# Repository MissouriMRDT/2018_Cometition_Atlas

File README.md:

# 2018_Cometition_Atlas
All Hardware and Software Files used in the 2018 Competition

How to add repos to this while retaining commit history:

1. Clone this repo onto your pc
2. Make branch on here for the repo you're about to copy in
3. Make sure that you've merged the final release branch of the target repo into master
4. In gitshell inside of the 2018 Competition Atlas folder:

git checkout [name of branch you're going to copy the repo into]

git remote add x [url of deprecated repo]

git fetch x

git merge x/master --allow-unrelated-histories

git remote rm x

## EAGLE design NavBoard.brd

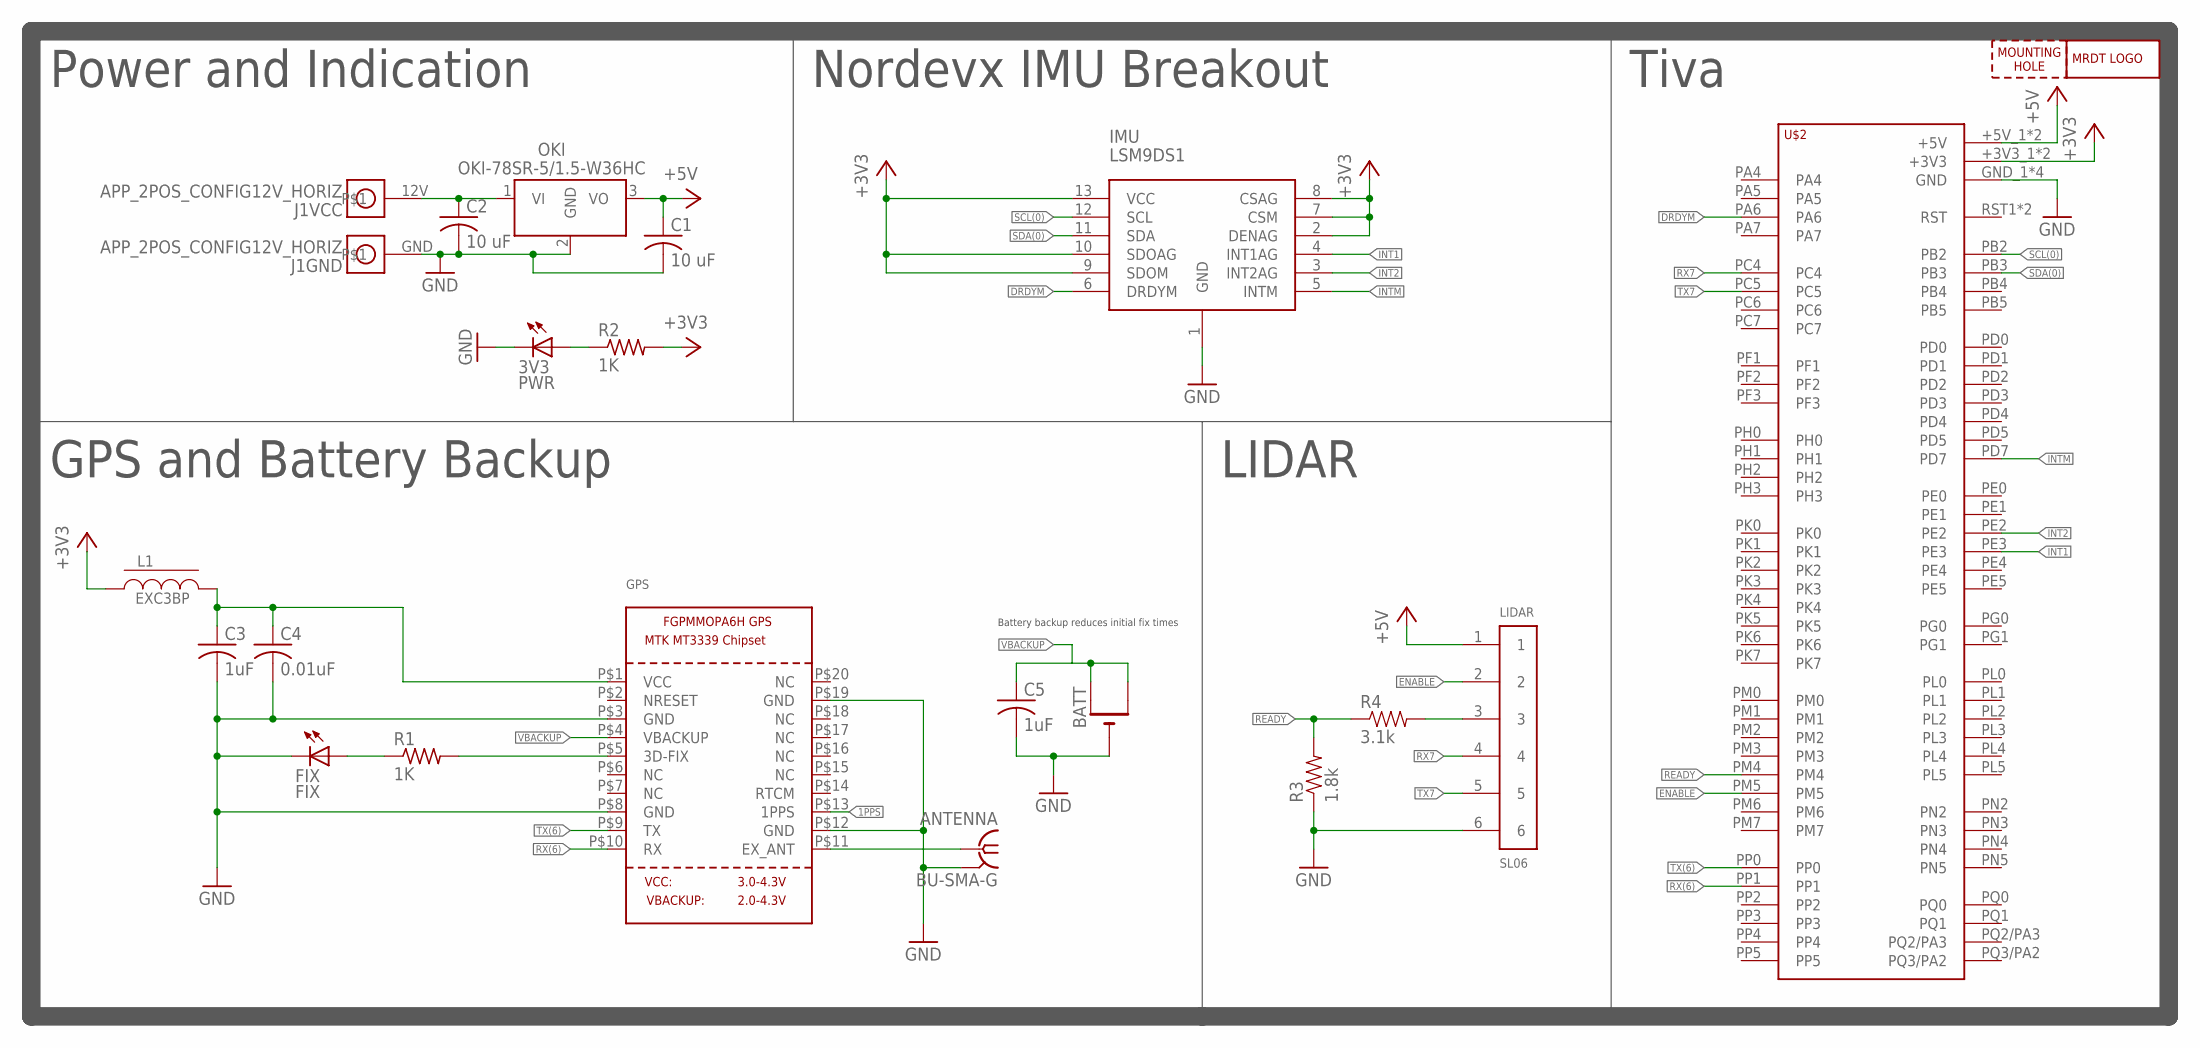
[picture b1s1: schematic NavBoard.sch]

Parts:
3V3: PWR; CHIPLED_0805
ANTENNA: BU-SMA-G
BATT: CR1220SMT; CR1220-SMD
C1, C2: 10 uF; C1206
C3, C5: 1uF; C0805
C4: 0.01uF; C0805
FIX: FIX; CHIPLED_0805
GPS: GPS_FGPMMOPA6H; FGPMMOPA6H
H1: MOUNTING_HOLE#6; #6_SCREW
IMU: LSM9DS1; LSM9DS1_BREAKOUT
J1: APP_2POS_CONFIG12V_HORIZ; APP45_12V_HORIZ_CONFIG
L1: EXC3BP; L0603
LIDAR: SL06; MOLEX_SL_06_TH
LOGO1: MRDT_LOGO
OKI: OKI-78SR-5/1.5-W36HC; OKI-78SR_HORIZ
R1, R2: 1K; M0805
R3: 1.8k; 0805
R4: 3.1k; 0805
U$2: TIVA-1294; TIVA-C-CONNECTED

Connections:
1PPS: GPS.P$13 (1PPS)
3V3: C3.1, C4.1, GPS.P$1 (VCC), L1.2
12V: C2.1, J1.12V, OKI.1 (VI)
+3V3: IMU.2 (DENAG), IMU.7 (CSM), IMU.8 (CSAG), IMU.9 (SDOM), IMU.10 (SDOAG), IMU.13 (VCC), L1.1, R2.2, U$2.+3V3_1 (+3V3), U$2.+3V3_2 (+3V3)
+5V: C1.1, LIDAR.1, OKI.3 (VO), U$2.+5V_1 (+5V), U$2.+5V_2 (+5V)
DRDYM: IMU.6 (DRDYM), U$2.PA6
ENABLE: LIDAR.2, U$2.PM5
GND: 3V3.C, ANTENNA.2, ANTENNA.3 (2), ANTENNA.4 (2), ANTENNA.5 (2), BATT.-, C1.2, C2.2, C3.2, C4.2, C5.2, FIX.C, GPS.P$3 (GND), GPS.P$8 (GND), GPS.P$12 (GND), GPS.P$19 (GND), IMU.1 (GND), J1.GND, LIDAR.6, OKI.2 (GND), R3.1, U$2.GND_1 (GND), U$2.GND_2 (GND), U$2.GND_3 (GND), U$2.GND_4 (GND)
INT1: IMU.4 (INT1AG), U$2.PE3
INT2: IMU.3 (INT2AG), U$2.PE2
INTM: IMU.5 (INTM), U$2.PD7
unnamed: FIX.A, R1.1
unnamed: GPS.P$5 (3D-FIX), R1.2
unnamed: 3V3.A, R2.1
unnamed: ANTENNA.1, GPS.P$11 (EX_ANT)
unnamed: LIDAR.3, R4.2
READY: R3.2, R4.1, U$2.PM4
RX7: LIDAR.4, U$2.PC4
RX(6): GPS.P$10 (RX), U$2.PP1
SCL(0): IMU.12 (SCL), U$2.PB2
SDA(0): IMU.11 (SDA), U$2.PB3
TX7: LIDAR.5, U$2.PC5
TX(6): GPS.P$9 (TX), U$2.PP0
VBACKUP: BATT.+$1 (+), BATT.+$2 (+1), C5.1, GPS.P$4 (VBACKUP)

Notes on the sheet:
Power and Indication
Nordevx IMU Breakout
Tiva
GPS and Battery Backup
LIDAR
Battery backup reduces initial fix times

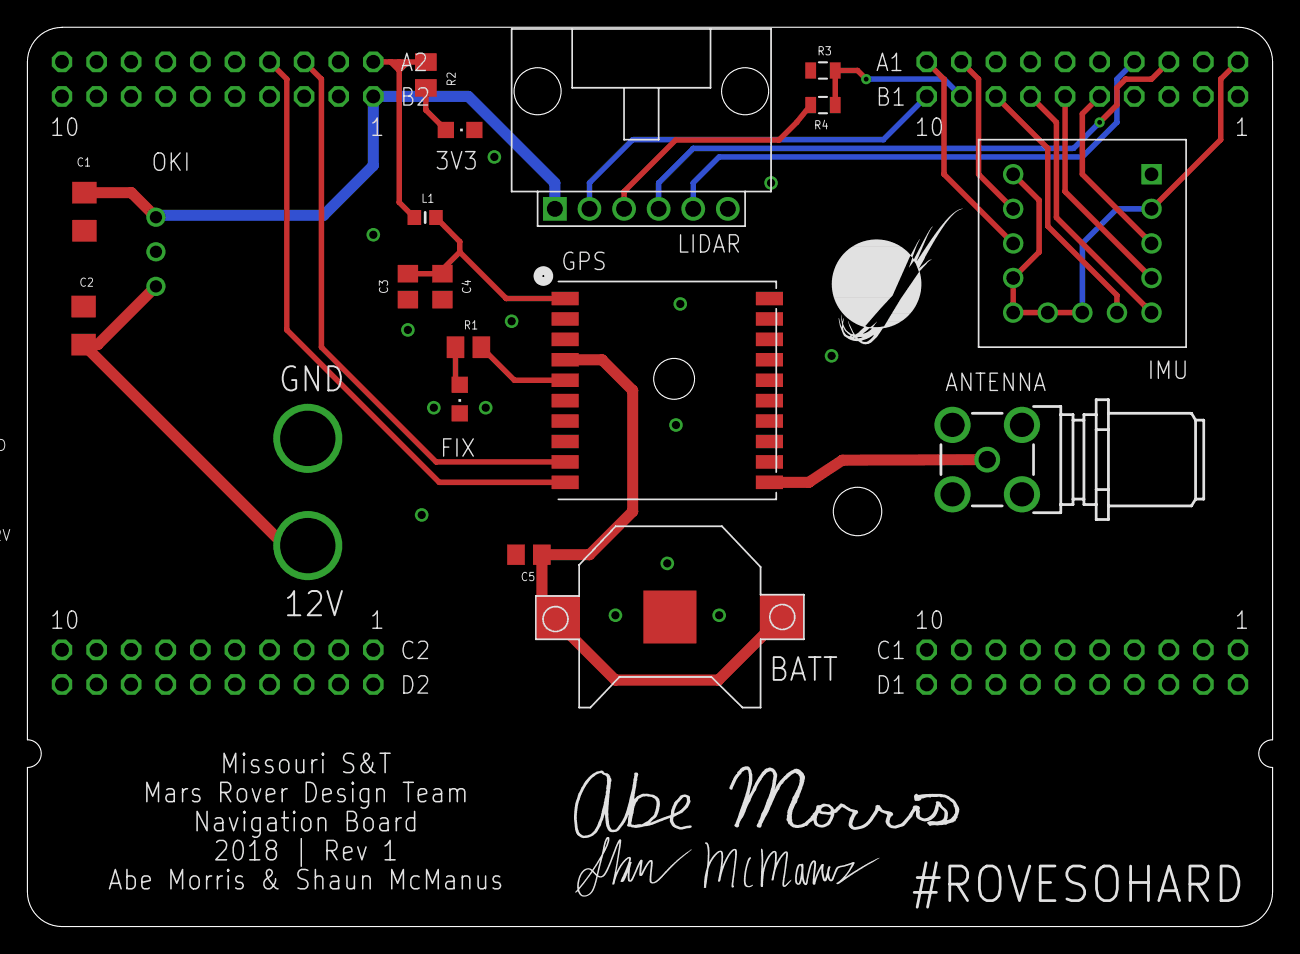
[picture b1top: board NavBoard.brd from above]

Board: 2 copper layers, 91.4 x 66.0 mm, 24 parts (0 on the bottom side), 23 nets.

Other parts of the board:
U$1: ABE_MORRIS_SIGNATURE
U$3: SHAUN_MCMANUS_SIGNATURE

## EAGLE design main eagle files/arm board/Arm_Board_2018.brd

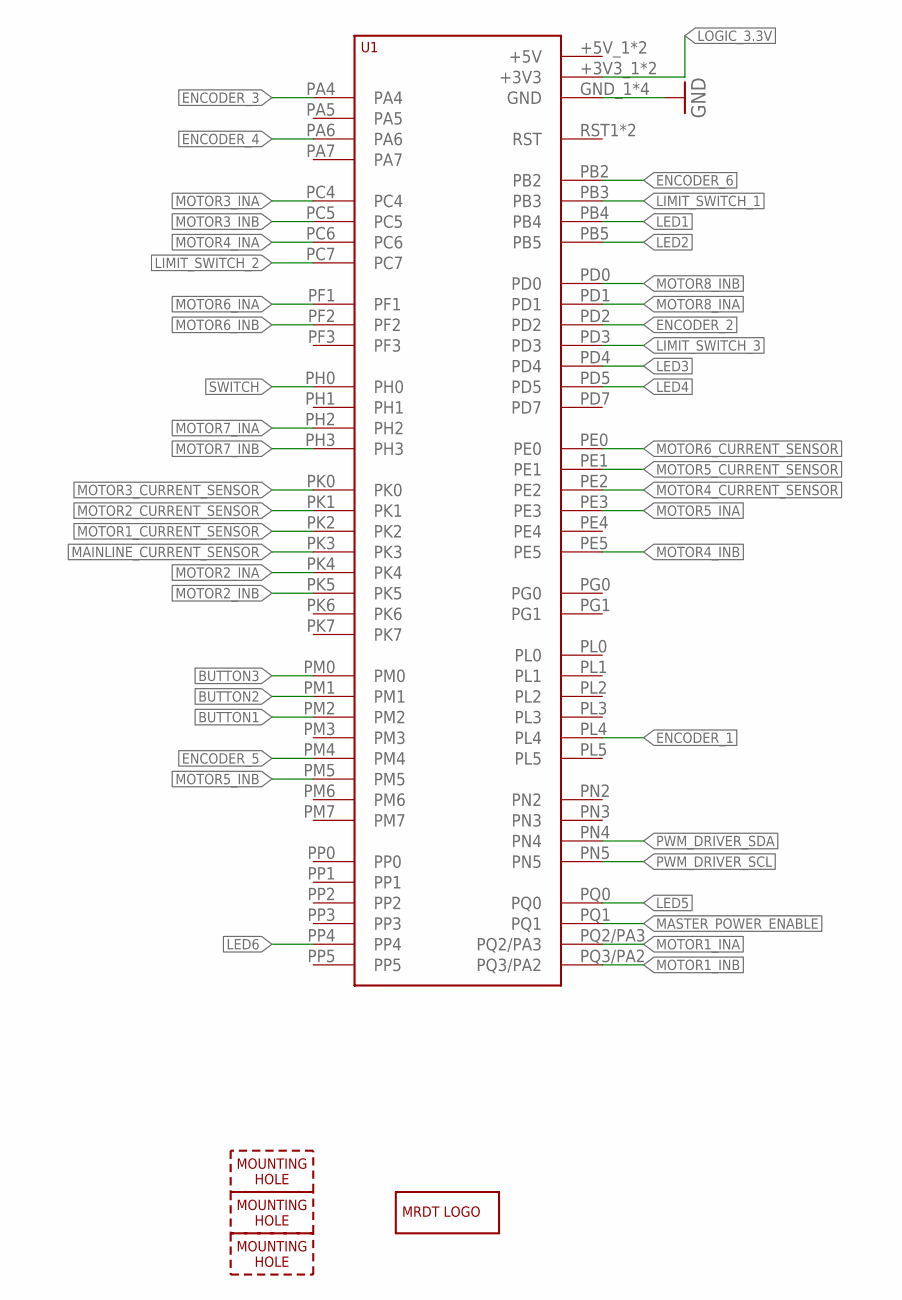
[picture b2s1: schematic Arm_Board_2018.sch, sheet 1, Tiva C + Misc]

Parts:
H1, H2, H3: MOUNTING_HOLE#6; #6_SCREW
LOGO1: MRDT_LOGO
U1: TIVA-1294; TIVA-C-CONNECTED

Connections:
BUTTON1: U1.PM2; also elsewhere on the board
BUTTON2: U1.PM1; also elsewhere on the board
BUTTON3: U1.PM0; also elsewhere on the board
ENCODER_1: U1.PL4; also elsewhere on the board
ENCODER_2: U1.PD2; also elsewhere on the board
ENCODER_3: U1.PA4; also elsewhere on the board
ENCODER_4: U1.PA6; also elsewhere on the board
ENCODER_5: U1.PM4; also elsewhere on the board
ENCODER_6: U1.PB2; also elsewhere on the board
GND: U1.GND_1 (GND), U1.GND_2 (GND), U1.GND_3 (GND), U1.GND_4 (GND); also elsewhere on the board
LED1: U1.PB4; also elsewhere on the board
LED2: U1.PB5; also elsewhere on the board
LED3: U1.PD4; also elsewhere on the board
LED4: U1.PD5; also elsewhere on the board
LED5: U1.PQ0; also elsewhere on the board
LED6: U1.PP4; also elsewhere on the board
LIMIT_SWITCH_1: U1.PB3; also elsewhere on the board
LIMIT_SWITCH_2: U1.PC7; also elsewhere on the board
LIMIT_SWITCH_3: U1.PD3; also elsewhere on the board
LOGIC_3.3V: U1.+3V3_1 (+3V3), U1.+3V3_2 (+3V3); also elsewhere on the board
MAINLINE_CURRENT_SENSOR: U1.PK3; also elsewhere on the board
MASTER_POWER_ENABLE: U1.PQ1; also elsewhere on the board
MOTOR1_CURRENT_SENSOR: U1.PK2; also elsewhere on the board
MOTOR1_INA: U1.PQ2/PA3; also elsewhere on the board
MOTOR1_INB: U1.PQ3/PA2; also elsewhere on the board
MOTOR2_CURRENT_SENSOR: U1.PK1; also elsewhere on the board
MOTOR2_INA: U1.PK4; also elsewhere on the board
MOTOR2_INB: U1.PK5; also elsewhere on the board
MOTOR3_CURRENT_SENSOR: U1.PK0; also elsewhere on the board
MOTOR3_INA: U1.PC4; also elsewhere on the board
MOTOR3_INB: U1.PC5; also elsewhere on the board
MOTOR4_CURRENT_SENSOR: U1.PE2; also elsewhere on the board
MOTOR4_INA: U1.PC6; also elsewhere on the board
MOTOR4_INB: U1.PE5; also elsewhere on the board
MOTOR5_CURRENT_SENSOR: U1.PE1; also elsewhere on the board
MOTOR5_INA: U1.PE3; also elsewhere on the board
MOTOR5_INB: U1.PM5; also elsewhere on the board
MOTOR6_CURRENT_SENSOR: U1.PE0; also elsewhere on the board
MOTOR6_INA: U1.PF1; also elsewhere on the board
MOTOR6_INB: U1.PF2; also elsewhere on the board
MOTOR7_INA: U1.PH2; also elsewhere on the board
MOTOR7_INB: U1.PH3; also elsewhere on the board
MOTOR8_INA: U1.PD1; also elsewhere on the board
MOTOR8_INB: U1.PD0; also elsewhere on the board
PWM_DRIVER_SCL: U1.PN5; also elsewhere on the board
PWM_DRIVER_SDA: U1.PN4; also elsewhere on the board
SWITCH: U1.PH0; also elsewhere on the board

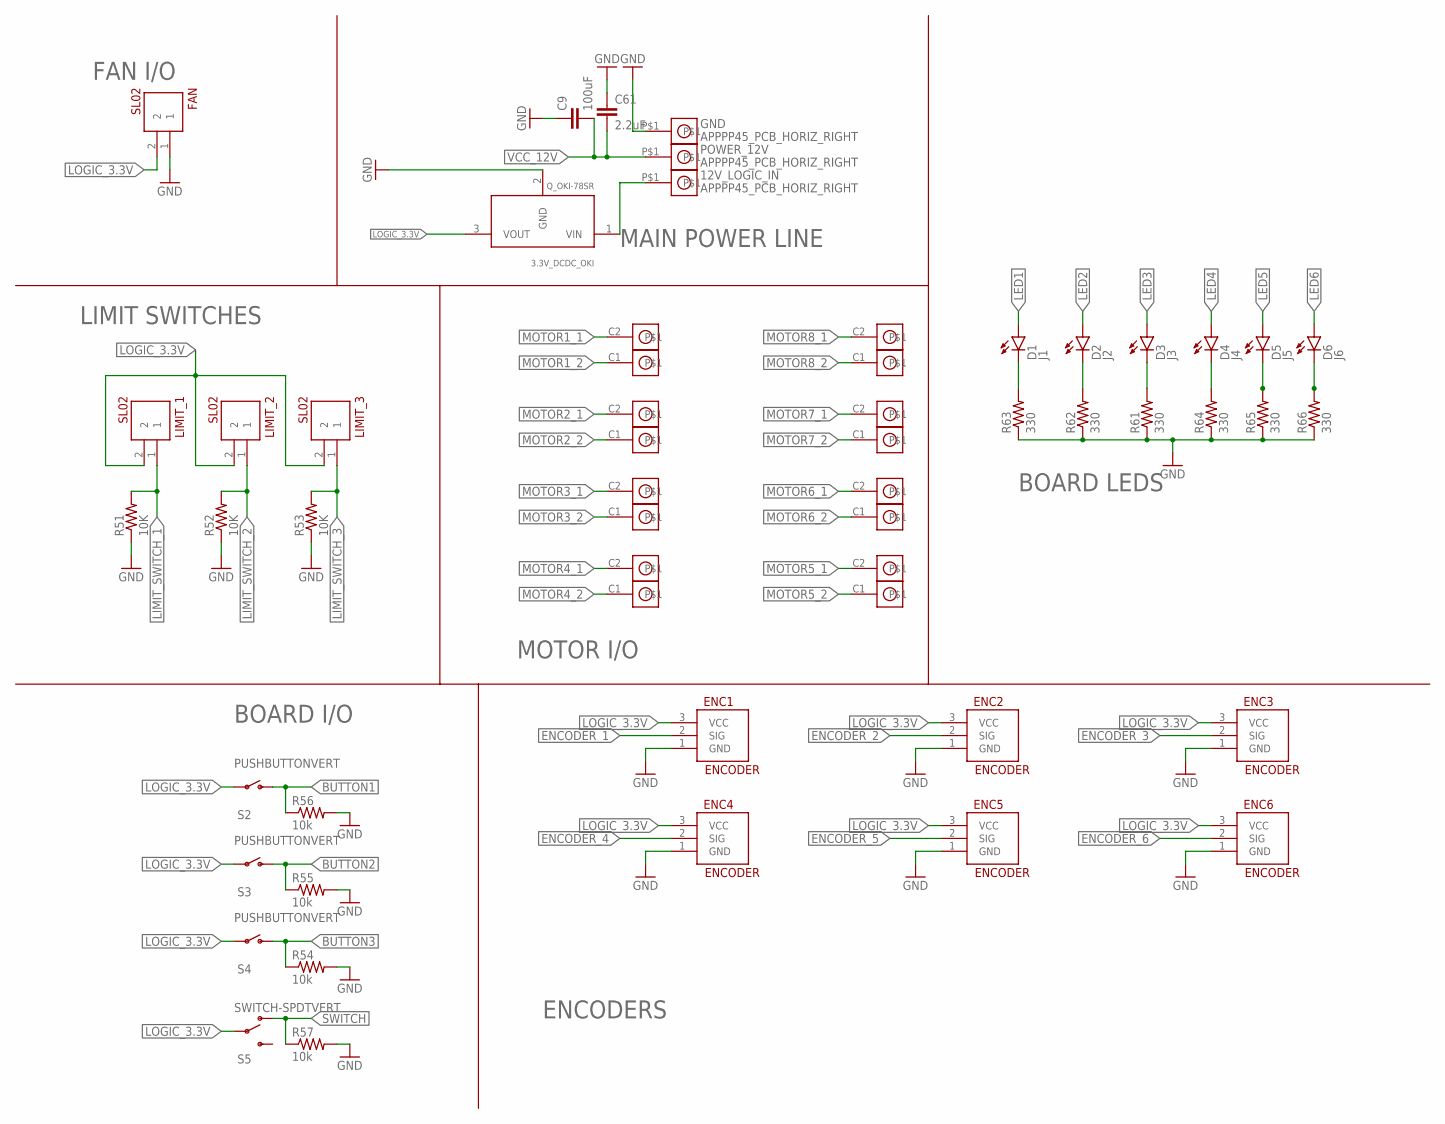
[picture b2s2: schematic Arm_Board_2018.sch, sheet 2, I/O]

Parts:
3.3V_DCDC_OKI: Q_OKI-78SR
12V_LOGIC_IN: APPPP45_PCB_HORIZ_RIGHT; APP45_PCB_HORIZ_RIGHT
C9: 100uF; 1210
C61: 2.2uF; 1206
D1: J1; LED-0603
D2: J2; LED-0603
D3: J3; LED-0603
D4: J4; LED-0603
D5: J5; LED-0603
D6: J6; LED-0603
ENC1, ENC2, ENC3, ENC4, ENC5, ENC6: ENCODER; MOLEX-70543-0002
FAN: SL02; MOLEX-70543-0001
GND: APPPP45_PCB_HORIZ_RIGHT; APP45_PCB_HORIZ_RIGHT
LIMIT_1, LIMIT_2, LIMIT_3: SL02; MOLEX-70543-0001
MOTOR1, MOTOR2, MOTOR3, MOTOR4, MOTOR5, MOTOR6, MOTOR7, MOTOR8: APP_2POS_CONFIGGENERAL_CONFIG; APP45_HORIZ_CONFIG
POWER_12V: APPPP45_PCB_HORIZ_RIGHT; APP45_PCB_HORIZ_RIGHT
R51, R52, R53: 10K; 0402-RES
R54, R55, R56, R57: 10k; 0402-RES
R61, R62, R63, R64, R65, R66: 330; 0402-RES
S2, S3, S4: PUSHBUTTONVERT; APEM-MJTP1243
S5: SWITCH-SPDTVERT; C&K-SS12D07VG4NSGAPA

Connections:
BUTTON1: R56.1, S2.P$2 (S); also elsewhere on the board
BUTTON2: R55.1, S3.P$2 (S); also elsewhere on the board
BUTTON3: R54.1, S4.P$2 (S); also elsewhere on the board
ENCODER_1: ENC1.2 (SIG); also elsewhere on the board
ENCODER_2: ENC2.2 (SIG); also elsewhere on the board
ENCODER_3: ENC3.2 (SIG); also elsewhere on the board
ENCODER_4: ENC4.2 (SIG); also elsewhere on the board
ENCODER_5: ENC5.2 (SIG); also elsewhere on the board
ENCODER_6: ENC6.2 (SIG); also elsewhere on the board
GND: 3.3V_DCDC_OKI.2 (GND), C9.1, C61.1, ENC1.1 (GND), ENC2.1 (GND), ENC3.1 (GND), ENC4.1 (GND), ENC5.1 (GND), ENC6.1 (GND), FAN.1, GND.P$1, R51.1, R52.1, R53.1, R54.2, R55.2, R56.2, R57.2, R61.1, R62.1, R63.1, R64.1, R65.1, R66.1; also elsewhere on the board
LED1: D1.A; also elsewhere on the board
LED2: D2.A; also elsewhere on the board
LED3: D3.A; also elsewhere on the board
LED4: D4.A; also elsewhere on the board
LED5: D5.A; also elsewhere on the board
LED6: D6.A; also elsewhere on the board
LIMIT_SWITCH_1: LIMIT_1.1, R51.2; also elsewhere on the board
LIMIT_SWITCH_2: LIMIT_2.1, R52.2; also elsewhere on the board
LIMIT_SWITCH_3: LIMIT_3.1, R53.2; also elsewhere on the board
LOGIC_3.3V: 3.3V_DCDC_OKI.3 (VOUT), ENC1.3 (VCC), ENC2.3 (VCC), ENC3.3 (VCC), ENC4.3 (VCC), ENC5.3 (VCC), ENC6.3 (VCC), FAN.2, LIMIT_1.2, LIMIT_2.2, LIMIT_3.2, S2.P$1, S3.P$1, S4.P$1, S5.P$2; also elsewhere on the board
MOTOR1_1: MOTOR1.C2; also elsewhere on the board
MOTOR1_2: MOTOR1.C1; also elsewhere on the board
MOTOR2_1: MOTOR2.C2; also elsewhere on the board
MOTOR2_2: MOTOR2.C1; also elsewhere on the board
MOTOR3_1: MOTOR3.C2; also elsewhere on the board
MOTOR3_2: MOTOR3.C1; also elsewhere on the board
MOTOR4_1: MOTOR4.C2; also elsewhere on the board
MOTOR4_2: MOTOR4.C1; also elsewhere on the board
MOTOR5_1: MOTOR5.C2; also elsewhere on the board
MOTOR5_2: MOTOR5.C1; also elsewhere on the board
MOTOR6_1: MOTOR6.C2; also elsewhere on the board
MOTOR6_2: MOTOR6.C1; also elsewhere on the board
MOTOR7_1: MOTOR7.C2; also elsewhere on the board
MOTOR7_2: MOTOR7.C1; also elsewhere on the board
MOTOR8_1: MOTOR8.C2; also elsewhere on the board
MOTOR8_2: MOTOR8.C1; also elsewhere on the board
unnamed: 3.3V_DCDC_OKI.1 (VIN), 12V_LOGIC_IN.P$1
unnamed: D1.C, R63.2
unnamed: D2.C, R62.2
unnamed: D6.C, R66.2
unnamed: D3.C, R61.2
unnamed: D4.C, R64.2
unnamed: D5.C, R65.2
SWITCH: R57.1, S5.P$3 (O); also elsewhere on the board
VCC_12V: C9.2, C61.2, POWER_12V.P$1; also elsewhere on the board

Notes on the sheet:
FAN I/O
MOTOR I/O
MAIN POWER LINE
LIMIT SWITCHES
ENCODERS
BOARD I/O
BOARD LEDS

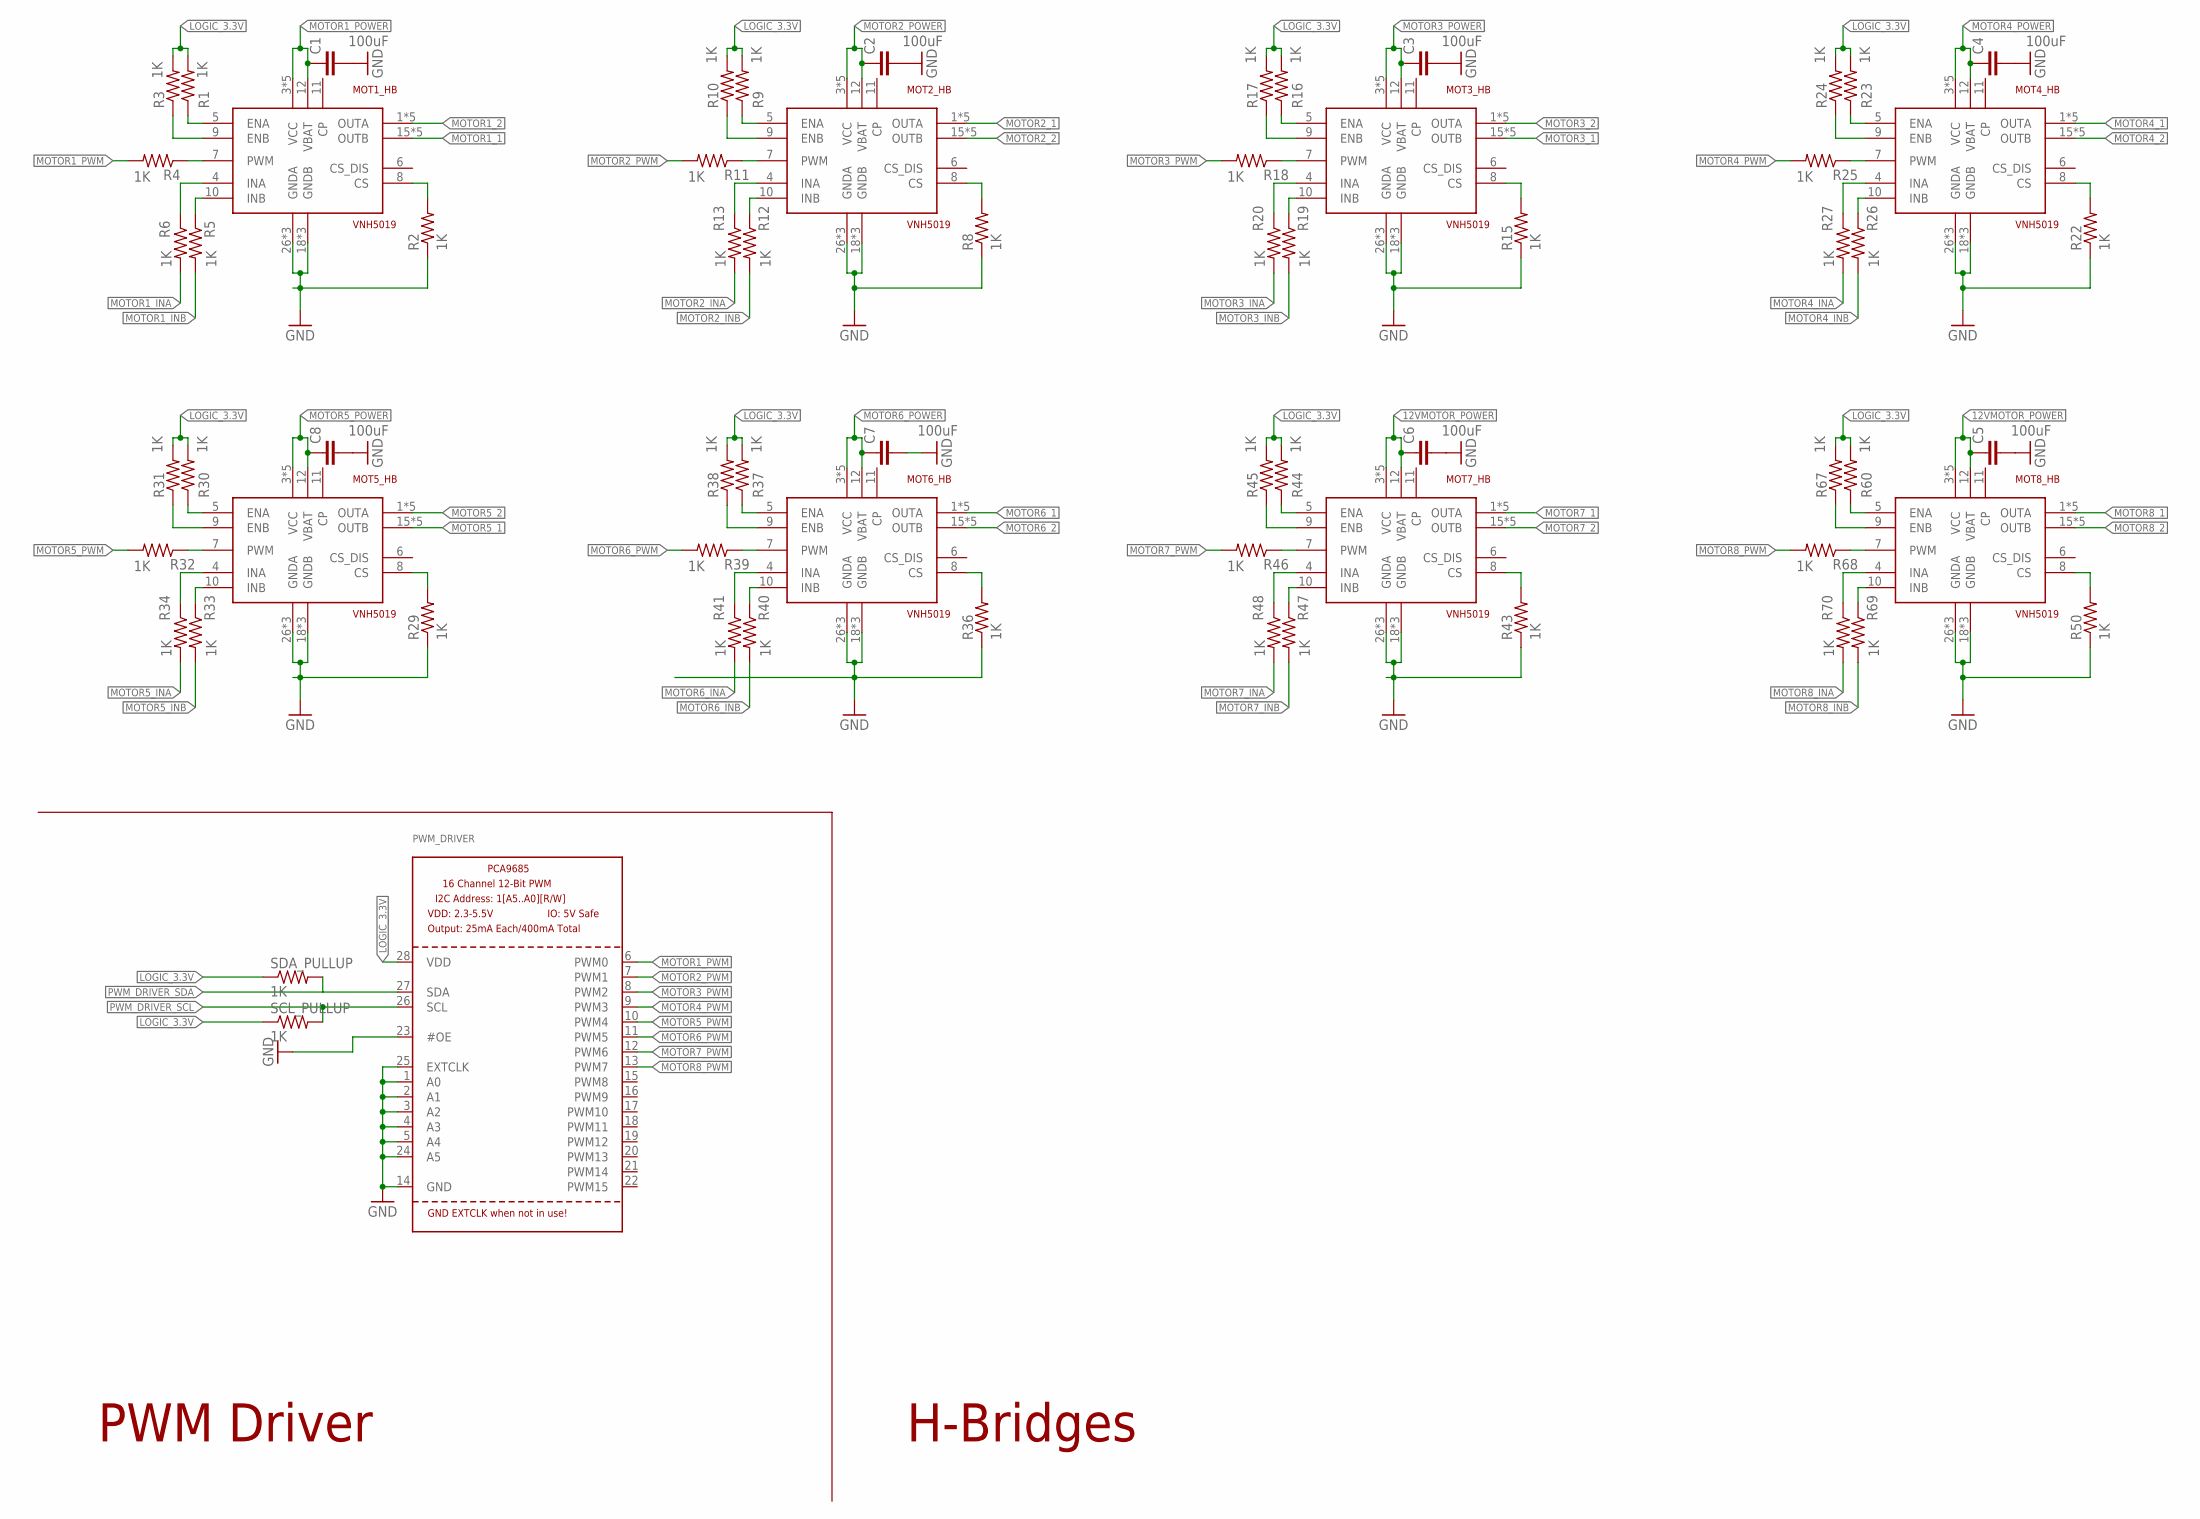
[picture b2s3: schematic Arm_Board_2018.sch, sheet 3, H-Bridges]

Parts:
C1, C2, C3, C4, C5, C6, C7, C8: 100uF; 1210
MOT1_HB, MOT2_HB, MOT3_HB, MOT4_HB, MOT5_HB, MOT6_HB, MOT7_HB, MOT8_HB: VNH5019; MULTIPOWERSO-30
PWM_DRIVER: PCA9685; TSSOP28
R1, R2, R3, R4, R5, R6, R8, R9, R10, R11, R12, R13, R15, R16, R17, R18, R19, R20, R22, R23, R24, R25, R26, R27, R29, R30, R31, R32, R33, R34, R36, R37, R38, R39, R40, R41, R43, R44, R45, R46, R47, R48, R50, R60, R67, R68, R69, R70: 1K; 0603-RES
SCL_PULLUP: 1K; 0402-RES
SDA_PULLUP: 1K; 0402-RES

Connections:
12VMOTOR_POWER: C5.1, C6.1, MOT7_HB.3 (VCC), MOT7_HB.12 (VBAT), MOT7_HB.13 (VCC), MOT7_HB.23 (VCC), MOT7_HB.VCC, MOT7_HB.VCC@1 (VCC), MOT8_HB.3 (VCC), MOT8_HB.12 (VBAT), MOT8_HB.13 (VCC), MOT8_HB.23 (VCC), MOT8_HB.VCC, MOT8_HB.VCC@1 (VCC); also elsewhere on the board
GND: C1.2, C2.2, C3.2, C4.2, C5.2, C6.2, C7.2, C8.2, MOT1_HB.18 (GNDB), MOT1_HB.19 (GNDB), MOT1_HB.20 (GNDB), MOT1_HB.26 (GNDA), MOT1_HB.27 (GNDA), MOT1_HB.28 (GNDA), MOT2_HB.18 (GNDB), MOT2_HB.19 (GNDB), MOT2_HB.20 (GNDB), MOT2_HB.26 (GNDA), MOT2_HB.27 (GNDA), MOT2_HB.28 (GNDA), MOT3_HB.18 (GNDB), MOT3_HB.19 (GNDB), MOT3_HB.20 (GNDB), MOT3_HB.26 (GNDA), MOT3_HB.27 (GNDA), MOT3_HB.28 (GNDA), MOT4_HB.18 (GNDB), MOT4_HB.19 (GNDB), MOT4_HB.20 (GNDB), MOT4_HB.26 (GNDA), MOT4_HB.27 (GNDA), MOT4_HB.28 (GNDA), MOT5_HB.18 (GNDB), MOT5_HB.19 (GNDB), MOT5_HB.20 (GNDB), MOT5_HB.26 (GNDA), MOT5_HB.27 (GNDA), MOT5_HB.28 (GNDA), MOT6_HB.18 (GNDB), MOT6_HB.19 (GNDB), MOT6_HB.20 (GNDB), MOT6_HB.26 (GNDA), MOT6_HB.27 (GNDA), MOT6_HB.28 (GNDA), MOT7_HB.18 (GNDB), MOT7_HB.19 (GNDB), MOT7_HB.20 (GNDB), MOT7_HB.26 (GNDA), MOT7_HB.27 (GNDA), MOT7_HB.28 (GNDA), MOT8_HB.18 (GNDB), MOT8_HB.19 (GNDB), MOT8_HB.20 (GNDB), MOT8_HB.26 (GNDA), MOT8_HB.27 (GNDA), MOT8_HB.28 (GNDA), PWM_DRIVER.1 (A0), PWM_DRIVER.2 (A1), PWM_DRIVER.3 (A2), PWM_DRIVER.4 (A3), PWM_DRIVER.5 (A4), PWM_DRIVER.14 (GND), PWM_DRIVER.23 (#OE), PWM_DRIVER.24 (A5), PWM_DRIVER.25 (EXTCLK), R2.1, R8.1, R15.1, R22.1, R29.1, R36.1, R43.1, R50.1; also elsewhere on the board
LOGIC_3.3V: PWM_DRIVER.28 (VDD), R1.2, R3.2, R9.2, R10.2, R16.2, R17.2, R23.2, R24.2, R30.2, R31.2, R37.2, R38.2, R44.2, R45.2, R60.2, R67.2, SCL_PULLUP.1, SDA_PULLUP.1; also elsewhere on the board
MOTOR1_1: MOT1_HB.15 (OUTB), MOT1_HB.16 (OUTB), MOT1_HB.21 (OUTB), MOT1_HB.OUTB, MOT1_HB.OUTB@1 (OUTB); also elsewhere on the board
MOTOR1_2: MOT1_HB.1 (OUTA), MOT1_HB.25 (OUTA), MOT1_HB.30 (OUTA), MOT1_HB.OUTA, MOT1_HB.OUTA@1 (OUTA); also elsewhere on the board
MOTOR1_INA: R6.2; also elsewhere on the board
MOTOR1_INB: R5.2; also elsewhere on the board
MOTOR1_POWER: C1.1, MOT1_HB.3 (VCC), MOT1_HB.12 (VBAT), MOT1_HB.13 (VCC), MOT1_HB.23 (VCC), MOT1_HB.VCC, MOT1_HB.VCC@1 (VCC); also elsewhere on the board
MOTOR1_PWM: PWM_DRIVER.6 (PWM0), R4.2
MOTOR2_1: MOT2_HB.1 (OUTA), MOT2_HB.25 (OUTA), MOT2_HB.30 (OUTA), MOT2_HB.OUTA, MOT2_HB.OUTA@1 (OUTA); also elsewhere on the board
MOTOR2_2: MOT2_HB.15 (OUTB), MOT2_HB.16 (OUTB), MOT2_HB.21 (OUTB), MOT2_HB.OUTB, MOT2_HB.OUTB@1 (OUTB); also elsewhere on the board
MOTOR2_INA: R13.2; also elsewhere on the board
MOTOR2_INB: R12.2; also elsewhere on the board
MOTOR2_POWER: C2.1, MOT2_HB.3 (VCC), MOT2_HB.12 (VBAT), MOT2_HB.13 (VCC), MOT2_HB.23 (VCC), MOT2_HB.VCC, MOT2_HB.VCC@1 (VCC); also elsewhere on the board
MOTOR2_PWM: PWM_DRIVER.7 (PWM1), R11.2
MOTOR3_1: MOT3_HB.15 (OUTB), MOT3_HB.16 (OUTB), MOT3_HB.21 (OUTB), MOT3_HB.OUTB, MOT3_HB.OUTB@1 (OUTB); also elsewhere on the board
MOTOR3_2: MOT3_HB.1 (OUTA), MOT3_HB.25 (OUTA), MOT3_HB.30 (OUTA), MOT3_HB.OUTA, MOT3_HB.OUTA@1 (OUTA); also elsewhere on the board
MOTOR3_INA: R20.2; also elsewhere on the board
MOTOR3_INB: R19.2; also elsewhere on the board
MOTOR3_POWER: C3.1, MOT3_HB.3 (VCC), MOT3_HB.12 (VBAT), MOT3_HB.13 (VCC), MOT3_HB.23 (VCC), MOT3_HB.VCC, MOT3_HB.VCC@1 (VCC); also elsewhere on the board
MOTOR3_PWM: PWM_DRIVER.8 (PWM2), R18.2
MOTOR4_1: MOT4_HB.1 (OUTA), MOT4_HB.25 (OUTA), MOT4_HB.30 (OUTA), MOT4_HB.OUTA, MOT4_HB.OUTA@1 (OUTA); also elsewhere on the board
MOTOR4_2: MOT4_HB.15 (OUTB), MOT4_HB.16 (OUTB), MOT4_HB.21 (OUTB), MOT4_HB.OUTB, MOT4_HB.OUTB@1 (OUTB); also elsewhere on the board
MOTOR4_INA: R27.2; also elsewhere on the board
MOTOR4_INB: R26.2; also elsewhere on the board
MOTOR4_POWER: C4.1, MOT4_HB.3 (VCC), MOT4_HB.12 (VBAT), MOT4_HB.13 (VCC), MOT4_HB.23 (VCC), MOT4_HB.VCC, MOT4_HB.VCC@1 (VCC); also elsewhere on the board
MOTOR4_PWM: PWM_DRIVER.9 (PWM3), R25.2
MOTOR5_1: MOT5_HB.15 (OUTB), MOT5_HB.16 (OUTB), MOT5_HB.21 (OUTB), MOT5_HB.OUTB, MOT5_HB.OUTB@1 (OUTB); also elsewhere on the board
MOTOR5_2: MOT5_HB.1 (OUTA), MOT5_HB.25 (OUTA), MOT5_HB.30 (OUTA), MOT5_HB.OUTA, MOT5_HB.OUTA@1 (OUTA); also elsewhere on the board
MOTOR5_INA: R34.2; also elsewhere on the board
MOTOR5_INB: R33.2; also elsewhere on the board
MOTOR5_POWER: C8.1, MOT5_HB.3 (VCC), MOT5_HB.12 (VBAT), MOT5_HB.13 (VCC), MOT5_HB.23 (VCC), MOT5_HB.VCC, MOT5_HB.VCC@1 (VCC); also elsewhere on the board
MOTOR5_PWM: PWM_DRIVER.10 (PWM4), R32.2
MOTOR6_1: MOT6_HB.1 (OUTA), MOT6_HB.25 (OUTA), MOT6_HB.30 (OUTA), MOT6_HB.OUTA, MOT6_HB.OUTA@1 (OUTA); also elsewhere on the board
MOTOR6_2: MOT6_HB.15 (OUTB), MOT6_HB.16 (OUTB), MOT6_HB.21 (OUTB), MOT6_HB.OUTB, MOT6_HB.OUTB@1 (OUTB); also elsewhere on the board
MOTOR6_INA: R41.2; also elsewhere on the board
MOTOR6_INB: R40.2; also elsewhere on the board
MOTOR6_POWER: C7.1, MOT6_HB.3 (VCC), MOT6_HB.12 (VBAT), MOT6_HB.13 (VCC), MOT6_HB.23 (VCC), MOT6_HB.VCC, MOT6_HB.VCC@1 (VCC); also elsewhere on the board
MOTOR6_PWM: PWM_DRIVER.11 (PWM5), R39.2
MOTOR7_1: MOT7_HB.1 (OUTA), MOT7_HB.25 (OUTA), MOT7_HB.30 (OUTA), MOT7_HB.OUTA, MOT7_HB.OUTA@1 (OUTA); also elsewhere on the board
MOTOR7_2: MOT7_HB.15 (OUTB), MOT7_HB.16 (OUTB), MOT7_HB.21 (OUTB), MOT7_HB.OUTB, MOT7_HB.OUTB@1 (OUTB); also elsewhere on the board
MOTOR7_INA: R48.2; also elsewhere on the board
MOTOR7_INB: R47.2; also elsewhere on the board
MOTOR7_PWM: PWM_DRIVER.12 (PWM6), R46.2
MOTOR8_1: MOT8_HB.1 (OUTA), MOT8_HB.25 (OUTA), MOT8_HB.30 (OUTA), MOT8_HB.OUTA, MOT8_HB.OUTA@1 (OUTA); also elsewhere on the board
MOTOR8_2: MOT8_HB.15 (OUTB), MOT8_HB.16 (OUTB), MOT8_HB.21 (OUTB), MOT8_HB.OUTB, MOT8_HB.OUTB@1 (OUTB); also elsewhere on the board
MOTOR8_INA: R70.2; also elsewhere on the board
MOTOR8_INB: R69.2; also elsewhere on the board
MOTOR8_PWM: PWM_DRIVER.13 (PWM7), R68.2
unnamed: MOT2_HB.8 (CS), R8.2
unnamed: MOT1_HB.8 (CS), R2.2
unnamed: MOT1_HB.5 (ENA), R1.1
unnamed: MOT1_HB.9 (ENB), R3.1
unnamed: MOT1_HB.7 (PWM), R4.1
unnamed: MOT1_HB.10 (INB), R5.1
unnamed: MOT1_HB.4 (INA), R6.1
unnamed: MOT2_HB.5 (ENA), R9.1
unnamed: MOT2_HB.9 (ENB), R10.1
unnamed: MOT2_HB.7 (PWM), R11.1
unnamed: MOT2_HB.10 (INB), R12.1
unnamed: MOT2_HB.4 (INA), R13.1
unnamed: MOT3_HB.8 (CS), R15.2
unnamed: MOT3_HB.5 (ENA), R16.1
unnamed: MOT3_HB.9 (ENB), R17.1
unnamed: MOT3_HB.7 (PWM), R18.1
unnamed: MOT3_HB.10 (INB), R19.1
unnamed: MOT3_HB.4 (INA), R20.1
unnamed: MOT4_HB.8 (CS), R22.2
unnamed: MOT4_HB.5 (ENA), R23.1
unnamed: MOT4_HB.9 (ENB), R24.1
unnamed: MOT4_HB.7 (PWM), R25.1
unnamed: MOT4_HB.10 (INB), R26.1
unnamed: MOT4_HB.4 (INA), R27.1
unnamed: MOT5_HB.8 (CS), R29.2
unnamed: MOT5_HB.5 (ENA), R30.1
unnamed: MOT5_HB.9 (ENB), R31.1
unnamed: MOT5_HB.7 (PWM), R32.1
unnamed: MOT5_HB.10 (INB), R33.1
unnamed: MOT5_HB.4 (INA), R34.1
unnamed: MOT6_HB.8 (CS), R36.2
unnamed: MOT6_HB.5 (ENA), R37.1
unnamed: MOT6_HB.9 (ENB), R38.1
unnamed: MOT6_HB.7 (PWM), R39.1
unnamed: MOT6_HB.10 (INB), R40.1
unnamed: MOT6_HB.4 (INA), R41.1
unnamed: MOT7_HB.8 (CS), R43.2
unnamed: MOT7_HB.5 (ENA), R44.1
unnamed: MOT7_HB.9 (ENB), R45.1
unnamed: MOT7_HB.7 (PWM), R46.1
unnamed: MOT7_HB.10 (INB), R47.1
unnamed: MOT7_HB.4 (INA), R48.1
unnamed: MOT8_HB.8 (CS), R50.2
unnamed: MOT8_HB.5 (ENA), R60.1
unnamed: MOT8_HB.9 (ENB), R67.1
unnamed: MOT8_HB.7 (PWM), R68.1
unnamed: MOT8_HB.10 (INB), R69.1
unnamed: MOT8_HB.4 (INA), R70.1
PWM_DRIVER_SCL: PWM_DRIVER.26 (SCL), SCL_PULLUP.2; also elsewhere on the board
PWM_DRIVER_SDA: PWM_DRIVER.27 (SDA), SDA_PULLUP.2; also elsewhere on the board

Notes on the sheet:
PWM Driver
H-Bridges

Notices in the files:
parts and their libraries:
SparkFun-Resistors: Licensing: Creative Commons ShareAlike 4.0 International - https://creativecommons.org/licenses/by-sa/4.0
SparkFun-Resistors: Licensing: CC v3.0 Share-Alike You are welcome to use this library for commercial purposes.
